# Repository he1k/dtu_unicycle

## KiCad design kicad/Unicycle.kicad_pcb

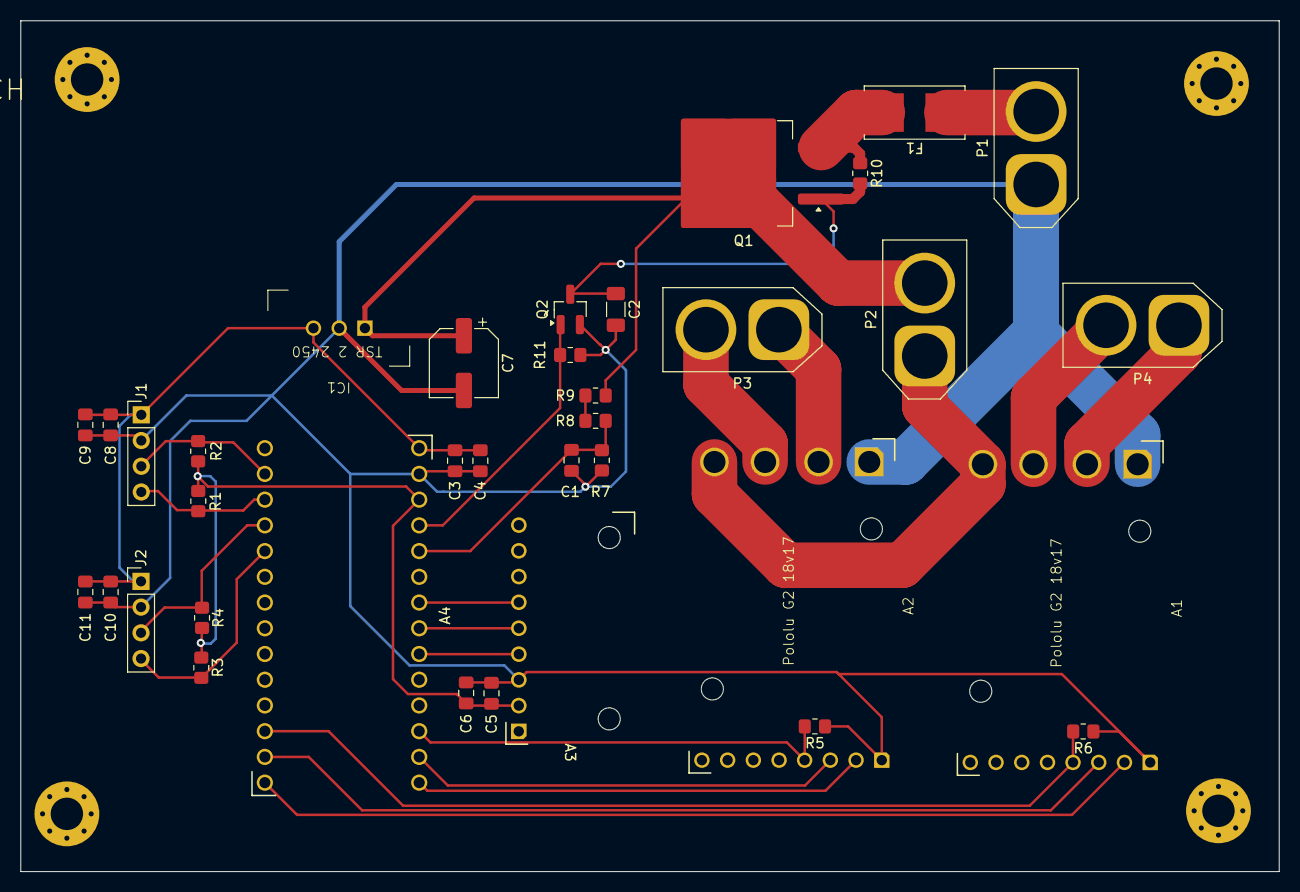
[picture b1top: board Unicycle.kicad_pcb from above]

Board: 2 copper layers, 124.2 x 84.0 mm, 40 parts (0 on the bottom side), 28 nets.

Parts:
A1, A2: Pololu G2 18v17; Pololu G2 18v17 Text Up
A3: Pololu LSM6DSO; PololuLSM6DSO Text Up
A4: Teensy 4.0; Teensy40 Simple
C1, C4, C6, C9, C11: 100nF; C_0805_2012Metric_Pad1.18x1.45mm_HandSolder
C2: 10uF; C_1206_3216Metric_Pad1.33x1.80mm_HandSolder
C3: 4u7F; C_0805_2012Metric_Pad1.18x1.45mm_HandSolder
C5, C8, C10: 1uF; C_0805_2012Metric_Pad1.18x1.45mm_HandSolder
C7: 47uF; CP_Elec_6.3x3.9
F1: Fuse; Fuseholder_Littelfuse_Nano2_154x
H1, H2, H3, H4: MountingHole_Pad; MountingHole_3.2mm_M3_Pad_Via
IC1: TSR 2 2450
J1, J2: HEDS 5500 A; PinHeader_1x04_P2.54mm_Vertical
P1: Battery Connector; AMASS_XT60-M_1x02_P7.20mm_Vertical
P2: Safety Switch Connector; AMASS_XT60-F_1x02_P7.20mm_Vertical
P3: Motor Connector Pitch; AMASS_XT60-F_1x02_P7.20mm_Vertical
P4: Motor Connector Roll; AMASS_XT60-F_1x02_P7.20mm_Vertical
Q1: DMP4010SK3Q-13; TO-263-2
Q2: SI2318A-TP; SOT-23_Handsoldering
R1, R2, R3, R4: 1.8k; R_0805_2012Metric_Pad1.20x1.40mm_HandSolder
R5, R6, R7: 10k; R_0805_2012Metric_Pad1.20x1.40mm_HandSolder
R8, R9: 47k; R_0805_2012Metric_Pad1.20x1.40mm_HandSolder
R10: 220k; R_0805_2012Metric_Pad1.20x1.40mm_HandSolder
R11: 4.7k; R_0805_2012Metric_Pad1.20x1.40mm_HandSolder

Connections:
+3.3V: A3.2 (VIN), A4.26 (3V3), C5.1, C6.1, R1.1, R2.1, R3.1, R4.1
+5V: A4.28 (VIN), C3.1, C4.1, C8.1, C9.1, C10.1, C11.1, IC1.3 (+Vout), J1.1, J2.1
+BATT: C7.1, IC1.1 (+Vin), P2.2, Q1.2 (D), R9.1
DIR_PITCH: A2.2 (DIR), A4.15 (13_SCK_CRX1_LED)
DIR_ROLL: A1.2 (DIR), A4.14 (12_MISO_MQSL)
ENC_A_PITCH: A4.4 (2_OUT2), J2.3, R4.2
ENC_A_ROLL: A4.2 (0_RX1_CRX2_CS1), J1.3, R2.2
ENC_B_PITCH: A4.5 (3_LRCLK2), J2.4, R3.2
ENC_B_ROLL: A4.3 (1_TX1_CTX2_MISO1), J1.4, R1.2
GND: A1.1 (GND), A1.9 (GND_M), A2.1 (GND), A2.9 (GND_M), A3.3 (GND), A4.1 (GND), A4.27 (GND), C1.2, C2.2, C3.2, C4.2, C5.2, C6.2, C7.2, C8.2, C9.2, C10.2, C11.2, H1.1, H2.1, H3.1, H4.1, IC1.2 (GND), J1.2, J2.2, P1.1, Q2.2 (S), R5.1, R6.1, R7.2, R11.2
unnamed: F1.1, P1.2
unnamed: C2.1, Q1.1 (G), Q2.3 (D), R10.2
unnamed: F1.2, Q1.3 (S), R10.1
unnamed: R8.1, R9.2
OUTA_PITCH: A2.11 (OUTA), P3.2
OUTA_ROLL: A1.11 (OUTA), P4.2
OUTB_PITCH: A2.10 (OUTB), P3.1
OUTB_ROLL: A1.10 (OUTB), P4.1
PWM_PITCH: A2.3 (PWM), A4.16 (14_A0_TX3_SPDIF_OUT)
PWM_ROLL: A1.3 (PWM), A4.13 (11_MOSI_CTX1)
PWR_ENABLE: A4.25 (23_A9_CRX1_MCLK1), Q2.1 (G), R11.1
SA0: A3.6 (SA0), A4.22 (20_A6_TX5_LRCLK1)
SCL: A3.5 (SCL), A4.21 (19_A5_SCL0)
SDA: A3.4 (SDA), A4.20 (18_A4_SDA0)
SLP_PITCH: A2.4 (#SLP), A4.17 (15_A1_RX3_SPDIF_IN), R5.2
SLP_ROLL: A1.4 (#SLP), A4.12 (10_CS_MQSR), R6.2
VBAT_MEAS: A4.24 (22_A8_CTX1), C1.1, R7.1, R8.2
VM_LIM: A1.12 (VM), A2.12 (VM), P2.1

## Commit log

2023-07-02 init
